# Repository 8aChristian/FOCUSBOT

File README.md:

# FOCUSBOT: Open-Source Autonomous AI Desktop Companion Robot

<p align="center">

</p>

---

## 📖 Índice General

1. [Descripción del Proyecto](#-descripción-del-proyecto)
2. [Arquitectura Mecánica y Carcasa DFA](#-arquitectura-mecánica-y-carcasa-dfa)
3. [Guía de Impresión 3D](#-guía-de-impresión-3d-paso-a-paso)
4. [Guía de Ensamblaje Mecatrónico](#-guía-de-ensamblaje-mecatrónico-paso-a-paso)
5. [Arquitectura Electrónica y PCBs](#-arquitectura-electrónica-y-pcbs)
6. [Guía de Carga de Firmware (PlatformIO)](#-guía-de-carga-de-firmware)
7. [Configuración de la IA y APIs de LLM](#-configuración-de-la-ia-y-apis-de-llm)
8. [Expresiones de Ojos y Movimientos Cutes](#-expresiones-de-ojos-y-movimientos-cutes)
9. [Lista de Materiales (BOM)](#-lista-de-materiales-bom)
10. [Licencia y Comunidad](#-licencia-y-comunidad)

---

## 🤖 Descripción del Proyecto

**FocusBot** es un robot de escritorio autónomo, compacto (**8.0 cm** de altura) y de código abierto diseñado como compañero de productividad, estudio e investigación mecatrónica. Equipado con visión por computadora, cuello articulado, locomoción diferencial, sintetizador de audio digital, micrófono MEMS y una pantalla IPS panorámica de 2.0 pulgadas con ojos procedurales bio-inspirados estilo Cozmo/Anki, FocusBot monitoriza tus sesiones de estudio, previene la procrastinación y te acompaña con una personalidad tierna y robótica mediante Modelos de Lenguaje (LLMs).

Es **100% Hardware y Software Libre**, optimizado para fabricarse con impresoras 3D domésticas (FDM/Resina) y PCBs de 2 capas estándar.

---

## 📐 Arquitectura Mecánica y Carcasa DFA

FocusBot incorpora una arquitectura monocoque **Top-Down DFA (Design for Assembly)** modelada en FreeCAD con el núcleo Open CASCADE:

### Características Clave de la Carcasa:
- **Carcasa Frontal Monolítica**: La cabeza frontal (`Carcasa_Cabeza_Frontal`) unifica el marco del visor y la estructura en una sola pieza sin juntas perimetrales ni holguras defectuosas. Cuenta con ventana activa de $43.5 \times 23.0\text{ mm}$ ($R=2.0\text{ mm}$) que aloja el panel LCD ST7789V de 2.0", y un orificio coaxial $\varnothing 2.6\text{ mm}$ para la cámara OV2640 a $Z = 71.0\text{ mm}$.
- **Orejas de Gato Bajas y Orgánicas**: Orejas curvadas y redondeadas de $5.3\text{ mm}$ de elevación sobre el techo, con cierre en vértice suave (cero tapas cónicas ni discos planos).
- **Difusor LED de Pecho en Forma Stadium (Cápsula Redondeada)**: Ranura frontal horizontal en el pecho de $19.6 \times 5.4\text{ mm}$ con bisel embutido de $23.6 \times 7.8\text{ mm}$ y pinhole de micrófono centrado arriba ($Z = 32.2\text{ mm}$), diseñada para emitir el brillo cyan característico del robot.
- **Tornillería Invisible y Cierre Bottom-Up**: La tapa del torso se fija mediante 4 tornillos M2 introducidos desde la base inferior hacia bosses ciegos en la cúpula, dejando el capó exterior 100% limpio y liso.
- **Cuello Flotante sin Fricción**: Holgura perimetral de aire de $0.80\text{ mm}$ entre cabeza y torso alrededor de una tornamesa de $\varnothing 18.0\text{ mm}$, garantizando rotación libre de -90° a +90° con $0.0000\text{ mm}^3$ de colisión.
- **Plano de Suelo Cinemático ($Z = 0.00\text{ mm}$)**: 4 puntos de apoyo coplanares formados por 2 ruedas cilíndricas lisas de tracción ($\varnothing 34.0\text{ mm}$) y 2 bolas de rodamiento omnidireccionales de acero ($\varnothing 8.0\text{ mm}$).

---

## 🖨️ Guía de Impresión 3D Paso a Paso

Todas las piezas se encuentran en formato `.stl` y `.step` en [`cad/stl/`](cad/stl/) y [`cad/3d_print_ready/`](cad/3d_print_ready/).

### Tabla de Piezas y Materiales:

| Pieza STL | Archivo STL | Material Recomendado | Color | Cant. | Soportes |
| :--- | :--- | :--- | :--- | :---: | :---: |
| **Cabeza Frontal** | `01_Carcasa_Cabeza_Frontal.stl` | PLA+ / PETG | Blanco Mate / Crema | 1 | No |
| **Cabeza Trasera + Orejas** | `02_Carcasa_Cabeza_Trasera.stl` | PLA+ / PETG | Blanco Mate / Crema | 1 | Solo en cuello (árbol) |
| **Chasis Torso Base** | `03_Carcasa_Torso_Chasis.stl` | PLA+ / PETG | Blanco Mate / Crema | 1 | No (apoyo plano) |
| **Tapa Superior Torso** | `04_Carcasa_Torso_Tapa.stl` | PLA+ / PETG | Blanco Mate / Crema | 1 | No |
| **Difusor LED Pecho** | `06_Difusor_Luz_Pecho.stl` | PETG Translúcido / Resina Clear | Blanco Natural / Clear | 1 | No |
| **Rueda Tracción Izq.** | `07_Rueda_Traccion_L.stl` | PLA+ o TPU 95A | Negro / Gris Oscuro | 1 | No |
| **Rueda Tracción Der.** | `08_Rueda_Traccion_R.stl` | PLA+ o TPU 95A | Negro / Gris Oscuro | 1 | No |
| **Aro Rueda Izq.** | `09_Aro_Cyan_Rueda_L.stl` | PLA | Cyan / Azul Eléctrico | 1 | No |
| **Aro Rueda Der.** | `10_Aro_Cyan_Rueda_R.stl` | PLA | Cyan / Azul Eléctrico | 1 | No |

### Parámetros Óptimos de Laminación (PrusaSlicer / Bambu Studio / Cura / OrcaSlicer):
- **Altura de capa (Layer Height)**: `0.16 mm` (o `0.12 mm` para la cabeza frontal para lograr máxima suavidad en el marco de la pantalla).
- **Perímetros / Paredes**: `4 perímetros` (mínimo `1.6 mm` de grosor de pared para asegurar la firmeza de las roscas de tornillos M2).
- **Relleno (Infill)**: `20% a 25% Gyroid` o Honeycomb.
- **Capas superiores e inferiores**: 5 capas sólidas arriba, 4 abajo.
- **Soportes**: Desactivados por defecto. Si tu impresora tiene puentes limitados, activa únicamente **Tree Supports (Soportes Tipo Árbol)** con ángulo de voladizo de >60° en la carcasa trasera de la cabeza.
- **Orientación de impresión**:
  - `Carcasa_Torso_Chasis`: Base plana hacia la cama de impresión.
  - `Carcasa_Torso_Tapa`: Superficie plana de partición hacia la cama.
  - `Carcasa_Cabeza_Frontal`: Cara frontal orientada hacia arriba o cara plana de unión hacia la cama.
  - `Ruedas`: Cara externa plana asentada en la cama.

---

## 🛠️ Guía de Ensamblaje Mecatrónico Paso a Paso

```mermaid
flowchart TD
    A["1. Chasis Inferior: Insertar 2x Bolas 8mm y 2x Motores N20"] --> B["2. Batería: Colocar LiPo 500mAh en su bahía inferior"]
    B --> C["3. Mainboard: Fijar PCB con 4x M2x4mm y conectar motores"]
    C --> D["4. Pecho: Insertar difusor LED stadium en la ranura frontal"]
    D --> E["5. Torso: Cerrar Tapa y atornillar con 4x M2x10mm desde abajo"]
    E --> F["6. Cabeza: Asentar LCD 2.0'', cámara OV2640 y Headboard PCB"]
    F --> G["7. Instalar servo SG90 y parlante 1511 en carcasa trasera"]
    G --> H["8. Conectar FPC 24 pines a través del cuello rotativo"]
    H --> I["9. Cerrar cabeza con 4x M2x8mm y acoplar al servo horn"]
```

### Paso 1: Chasis Inferior y Locomoción
1. Inserta a presión las dos **bolas de rodamiento omnidireccionales de acero de $\varnothing 8.0\text{ mm}$** en sus alojamientos semiesféricos frontal y trasero del chasis base.
2. Coloca los dos **motores N20** en sus cunas laterales orientando los ejes hacia los orificios de rueda.
3. Introduce la **batería LiPo 1S de 500 mAh** ($38 \times 20 \times 7\text{ mm}$) en la bahía del suelo.

### Paso 2: Instalación de la Mainboard PCB
1. Posiciona la placa principal (`hardware/mainboard/focusbot_mainboard.kicad_pcb`) sobre los 4 pilares MH1-MH4 a $Z = 23.5\text{ mm}$.
2. Asegúrate de que el conector USB-C y el interruptor SW1 encajen perfectamente en sus aberturas traseras.
3. Atornilla la PCB con 4 tornillos M2 de 4 mm.
4. Suelda o conecta los terminales de los motores N20 a los pads `MOT_L` y `MOT_R` y el conector JST de la batería LiPo.

### Paso 3: Cierre del Torso y Difusor Frontal
1. Inserta a presión el **Difusor de luz de pecho** (`06_Difusor_Luz_Pecho.stl`) en la ranura redondeada frontal.
2. Pasa el cable plano FFC/FPC de 24 pines desde la Mainboard hacia arriba a través del conducto central de la tornamesa.
3. Coloca la **Carcasa Torso Tapa** sobre el chasis e introduce **4 tornillos M2 de 10 mm desde la parte inferior** del chasis para unir ambas mitades sólidamente.
4. Fija el brazo del servo (horn de 1 brazo) en el cajeado de la tornamesa con 2 tornillos M1.7.

### Paso 4: Ensamblaje de la Cabeza
1. En la **Carcasa Cabeza Frontal**, asienta el panel LCD ST7789V de 2.0" en su cuna interior cuidando que quede centrado con la ventana de visualización.
2. Coloca la cámara OV2640 en el cajeado superior con su lente alineado al orificio pinhole de $Z = 71.0\text{ mm}$.
3. Desliza la **Headboard PCB** verticalmente por las guías laterales hasta topar con el panel.
4. En la **Carcasa Cabeza Trasera**, monta el **micro-servo SG90** invertido (eje hacia abajo) fijándolo con 2 tornillos a sus aletas, y coloca el parlante miniatura 1511 en su alojamiento.
5. Conecta el cable FPC de 24 pines al conector ZIF de la Headboard.
6. Cierra la cabeza introduciendo **4 tornillos M2 de 8 mm** desde los avellanados de la carcasa trasera.
7. Presiona la cabeza sobre el eje estriado del servo acoplado a la tornamesa del torso.
8. Coloca a presión las ruedas de tracción y sus aros decorativos cyan en los ejes D-shaft de los motores N20.

---

## ⚡ Arquitectura Electrónica y PCBs

FocusBot cuenta con dos placas de circuito impreso diseñadas en KiCad 10 con **0 violaciones de DRC y 0 conexiones huérfanas**:

<p align="center">
  &nbsp;
  
</p>

### Distribución de Pines del ESP32-S3:

| Periférico | Función | Pines ESP32-S3 | Bus / Protocolo |
| :--- | :--- | :--- | :--- |
| **Pantalla LCD 2.0"** | ST7789V IPS (320x240) | MOSI: `GPIO35`, SCLK: `GPIO36`, DC: `GPIO47`, CS: `GPIO48` | SPI a 40 MHz |
| **Cámara IA** | OV2640 2MP DVP | SIOC: `GPIO4`, SIOD: `GPIO5`, XCLK: `GPIO6`, PCLK: `GPIO7`, HREF: `GPIO14`, VSYNC: `GPIO43`, D0-D7: `GPIO37,38,39,40,41,42,2,1` | DVP 8-bit + SCCB |
| **Audio DAC** | MAX98357A (Parlante) | BCLK: `GPIO12`, WS: `GPIO11`, DIN: `GPIO10` | I2S Digital |
| **Micrófono MEMS** | INMP441 (Voz / Caricias) | BCLK: `GPIO12`, WS: `GPIO11`, DOUT: `GPIO13` | I2S Digital |
| **Motores DC** | DRV8833 Dual H-Bridge | L_IN1: `GPIO15`, L_IN2: `GPIO16`, R_IN1: `GPIO17`, R_IN2: `GPIO18` | PWM 20 kHz (LEDC) |
| **Servo Cuello** | SG90 Pan (Giro Horiz.) | PWM: `GPIO21` | Servo 50 Hz |
| **Sensor Batería** | Divisor 1:2 LiPo | ADC: `GPIO44` | ADC1 Canal 3 |
| **Puerto Nativo USB** | Flasheo / JTAG / CDC | D-: `GPIO19`, D+: `GPIO20` | USB 2.0 FS Nativo |

---

## 💻 Guía de Carga de Firmware

El ESP32-S3-WROOM-1 cuenta con **controlador USB nativo en silicio**. No necesitas adaptadores UART externos (CH340/CP2102); la placa se programa directamente con un cable USB-C estándar conectado a la PC.

### Requisitos Previos:
1. Instalar [Visual Studio Code](https://code.visualstudio.com/).
2. Instalar la extensión **PlatformIO IDE** en VS Code (o instalar PlatformIO CLI vía `pip install platformio`).
3. Clonar este repositorio y abrir la carpeta del proyecto en VS Code.

### Compilación y Subida:

1. Abre una terminal en la raíz del proyecto y entra en `firmware`:
   ```powershell
   cd firmware
   ```

2. **Compilar el código**:
   ```powershell
   pio run
   ```
   *El sistema descargará automáticamente el toolchain de Espressif, FreeRTOS y las librerías necesarias.*

3. **Cargar el firmware en el robot**:
   Conecta FocusBot a la PC mediante el cable USB-C, enciende el interruptor SW1 y ejecuta:
   ```powershell
   pio run -t upload
   ```

4. **Abrir monitor serie para ver diagnósticos**:
   ```powershell
   pio device monitor -b 115200
   ```

> [!TIP]
> **Modo Bootloader Manual (en caso de puerto bloqueado):**
> Si el puerto COM no responde al flashear: mantén presionado el botón `BOOT` (SW_BOOT en la PCB), presiona y suelta el botón `RESET`, luego suelta `BOOT`. El ESP32-S3 entrará en modo de descarga forzado por hardware.

---

## 🧠 Configuración de la IA y APIs de LLM

FocusBot puede interactuar con Inteligencia Artificial conversacional a través de dos métodos:

### Método 1: App Móvil Companion por Bluetooth (Recomendado)
El robot actúa como periférico Bluetooth Low Energy (`FocusBot-Companion`). La aplicación en el teléfono procesa el audio con reconocimiento de voz y llama a la API de tu modelo preferido (ChatGPT, Claude o Gemini). La app retransmite el texto al robot, el cual parsea automáticamente las etiquetas de actuación.

### Método 2: Wi-Fi Directo en el Microcontrolador
Si deseas que el propio robot se conecte a internet y llame a las APIs directamente:

1. Ve a la carpeta `firmware/include/`.
2. Copia el archivo de ejemplo:
   ```powershell
   Copy-Item firmware/include/credentials.h.example firmware/include/credentials.h
   ```
3. Abre `firmware/include/credentials.h` y coloca tus credenciales:
   ```cpp
   // Red Wi-Fi
   #define FOCUSBOT_WIFI_SSID       "Mi_Casa_WiFi"
   #define FOCUSBOT_WIFI_PASSWORD   "MiContrasenaSegura"

   // Proveedor seleccionado ("OPENAI" | "GEMINI" | "CLAUDE" | "OLLAMA_LOCAL")
   #define LLM_PROVIDER             "OPENAI"

   // API Keys según tu cuenta:
   #define OPENAI_API_KEY           "sk-proj-xxxxxxxxxxxxxxxxxxxxxxxxxxxxxxxx"
   #define GEMINI_API_KEY           "AIzaSyxxxxxxxxxxxxxxxxxxxxxxxxxxxxxx"
   #define CLAUDE_API_KEY           "sk-ant-api03-xxxxxxxxxxxxxxxxxxxxxxxxx"
   ```

### Personalidad del Robot (System Prompt):
El archivo [`firmware/include/focusbot_llm_persona.h`](firmware/include/focusbot_llm_persona.h) contiene el prompt del sistema que define su comportamiento:
- **Voz y tono**: Robot cute, tierno, infantil pero inteligente, con sonidos robóticos cortos (*"bip bop!"*, *"whirrr"*).
- **Control de Actuación por Etiquetas**: El LLM emite etiquetas entre corchetes que el firmware traduce en hardware físico instantáneamente:

```text
[HAPPY]   -> Ojos cyan felices y alegres
[GLEE]    -> Arcos gigantes de felicidad extrema + sacudida de cuerpo
[AWE]     -> Ojos enormes brillantes de asombro + inclinación de cabeza
[WINK]    -> Guiño cómplice de un solo ojo
[HEART]   -> Ojos de corazones magenta + ronroneo
[WORRIED] -> Ojos preocupados (alerta cuando el usuario abandona la mesa)
[ANGRY]   -> Ojos rojos y ceño fruncido (alerta de procrastinación/celular)
[NOD]     -> Movimiento vertical del cuello diciendo "Sí"
[SHAKE]   -> Movimiento horizontal del cuello diciendo "No"
[TILT]    -> Inclinación lateral curiosa de la cabeza
[WIGGLE]  -> Bailecito de izquierda a derecha con las ruedas
[SPIN]    -> Giro de 360 grados de festejo
```

---

## 👀 Expresiones de Ojos y Movimientos Cutes

El motor visual procedural ([`display_engine.cpp`](firmware/src/display_engine.cpp)) implementa **31 estados emocionales** con renderizado multi-capa a 50 Hz en la pantalla IPS:

- **Efecto Glow Multi-capa**: Halo exterior atenuado, anillo medio difuso, núcleo cyan brillante, reflejos especulares orgánicos dobles y pupila oscura interior.
- **Seguimiento Facial en Tiempo Real**: La cámara OV2640 calcula el centroide de movimiento del usuario y los ojos lo siguen suavemente en los ejes X e Y (`setLookTarget(nx, ny)`).
- **Detector de Caricias (Petting Sensor)**: Al tocar suavemente la cabeza del robot, el micrófono MEMS detecta el patrón acústico de toque y activa ronroneo sintetizado con ojos de corazón.
- **Milestones de Concentración**: Cada 25 minutos de estudio continuo sin distracciones, el robot reproduce una fanfarria triunfal, sus ojos se tornan verde esmeralda brillante (`ILLUM_GREEN_WIN`) y ejecuta un giro de victoria (`spinJoy()`).

---

## 📋 SuperBOM: Lista Maestra de Componentes, Enlaces y Costos

Guía de compra optimizada para **máximo ahorro**, priorizando la fabricación de placas vírgenes (*bare PCBs*) y la adquisición de componentes por separado sin ensamblaje costoso de fábrica.

---

### 1. Componentes Externos (Modulares / Sin soldar a placa)

Se conectan directamente a las placas mediante cables y conectores:

| Componente | Enlaces de Compra Directa | Rango de Precio Estimado | Formato Habitual |
| :--- | :--- | :---: | :--- |
| **Batería LiPo 3.7V 500mAh**<br>(Conector JST-PH 2.0 mm) | • [AliExpress (Opción Económica)](https://www.aliexpress.com/item/32814862683.html)<br>• [Amazon (Envío Rápido)](https://www.amazon.com/dp/B0D3F67N6F) | **$4.00 – $9.00 USD** | Unidad con circuito de protección PCM integrado |
| **Micromotores N20 metálicos**<br>(6V 300 RPM con reductora) | • [AliExpress (N20 Gearmotor)](https://www.aliexpress.com/item/1005005519903657.html) | **$1.50 – $2.50 USD** | Por unidad (se requieren 2: Izquierdo y Derecho) |
| **Cables chicote JST-SH 1.0 mm**<br>(2 pines pre-crimpeados para motores/parlante) | • [AliExpress (Cables JST-SH 1.0 mm)](https://www.aliexpress.com/item/1005011595323701.html) | **$1.50 – $2.50 USD** | Paquete de 10 a 20 cables con conector hembra |
| **Micro-servo SG90 9g**<br>(Giro horizontal de cuello) | • [Amazon (Opción 1)](https://www.amazon.com/dp/B07L2SF3R4)<br>• [Amazon (Opción Alternativa)](https://www.amazon.com/dp/B01M5LIKLQ) | **$2.50 – $4.00 USD** | Unidad individual con juego de brazos/horns |
| **Micro-Parlante 1511**<br>(8 $\Omega$ 1W, $15 \times 11 \times 3.5\text{ mm}$) | • [AliExpress (Parlante 1511 Box)](https://www.aliexpress.com/i/1680403579.html) | **$0.90 – $1.70 USD** | Unidad suelta o lote de 5 a 10 piezas ($2.50 - $3.50) |
| **Cámara OV2640**<br>(Flex cinta 24 pines paso 0.5 mm) | • [AliExpress (OV2640 Módulo Cámara)](https://www.aliexpress.com/wholesale?catId=0&SearchText=OV2640) | **$2.80 – $4.50 USD** | Módulo de cámara con lente estándar |
| **Pantalla IPS LCD ST7789 2.0"**<br>(SPI 240x320, bare panel) | • [AliExpress (ST7789 2.0" IPS)](https://www.aliexpress.com/item/1005009314410563.html)<br>• [AliExpress (Opción Alternativa)](https://www.aliexpress.com/item/1005012615180387.html) | **$3.50 – $5.50 USD** | Panel individual IPS 240x320 |

---

### 2. Elementos de Interconexión Flexible y Zócalos ZIF

| Componente | Enlaces de Compra Directa | Rango de Precio Estimado | Formato Habitual |
| :--- | :--- | :---: | :--- |
| **Cable plano flexible FPC 24 pines**<br>(Paso 0.5 mm, Tipo A o Tipo B) | • [AliExpress (FPC 24P 0.5 mm)](https://www.aliexpress.com/i/1005006038283095.html)<br>• [AliExpress (Opción Alternativa)](https://www.aliexpress.com/i/4000022157163.html) | **$0.50 – $1.00 USD** | Paquete de 2 a 5 cables |
| **Conector ZIF 24 pines 0.5 mm SMD**<br>(Seguro abatible / Bottom Contact) | • [AliExpress (ZIF 24P 0.5 mm)](https://www.aliexpress.com/i/1005004233136813.html)<br>• [AliExpress (Opción Alternativa)](https://www.aliexpress.com/item/32850399481.html) | **$1.50 – $2.50 USD** | Tira o lote de 10 conectores para placa |
| **Conector hembra USB-C SMD 16 pines**<br>(Carga y datos nativos) | • [AliExpress (USB-C 16P SMD)](https://www.aliexpress.com/i/1005006257173539.html) | **$1.70 – $2.50 USD** | Lote de 5 a 10 conectores hembra |

---

### 3. Circuitos Integrados y Semiconductores para Soldar (SMD)

Comprados sueltos o en lote económico para soldar manualmente o con pasta de estaño y aire caliente:

| Componente / Circuito Integrado | Enlace Catálogo JLCPCB / LCSC / AliExpress | Precio Unitario Estimado |
| :--- | :--- | :---: |
| **ESP32-S3-WROOM-1-N8R8 / N16R8** | • [JLCPCB (C2913201)](https://jlcpcb.com/partdetail/3198299-ESP32_S3_WROOM_1N8R8/C2913201)<br>• [LCSC (C2913201)](https://www.lcsc.com/product-detail/C2913201.html) | **$3.50 – $4.40 USD** |
| **DRV8833PWP (Driver Puente H Dual)** | • [AliExpress (Chips DRV8833)](https://www.aliexpress.com/item/1005008600208107.html)<br>• [AliExpress (Opción 2)](https://www.aliexpress.com/item/1005005236496976.html) | **$0.70 – $1.30 USD** |
| **TP4056 (Cargador LiPo)** | • [AliExpress / LCSC](https://www.aliexpress.com/item/1005008600208107.html) | **$0.15 – $0.30 USD** |
| **DW01A + FS8205A (Protección LiPo)** | • LCSC / AliExpress (SOT-23-6 / TSSOP-8) | **$0.10 – $0.25 USD** |
| **SY8089AAAC (Regulador Step-Down 2A)** | • [LCSC (C78988)](https://www.lcsc.com/product-detail/DC-DC-Converters_Silergy-Corp-SY8089AAAC_C78988.html) | **$0.20 – $0.40 USD** |
| **MAX98357AETE+T (Amplificador I2S)** | • [JLCPCB (C910544)](https://jlcpcb.com/partdetail/MaximIntegrated-MAX98357AETET/C910544)<br>• [LCSC (C910544)](https://www.lcsc.com/product-detail/C910544.html) | **$0.90 – $1.20 USD** |
| **MPU-6050 (IMU 6 Ejes)** | • JLCPCB / LCSC / AliExpress (QFN-24) | **$1.20 – $2.20 USD** |
| **INMP441 (Micrófono MEMS LGA-9)** | • [AliExpress (INMP441 SMD suelto)](https://he.aliexpress.com/item/1005007633632817.html) | **$1.50 – $3.00 USD** |
| **Componentes Pasivos y Discretos 0603**<br>(Inductor 2.2µH, AO3401A, SS14, BAT54, R, C) | • Kits surtidos 0603 en AliExpress / LCSC | **$0.50 – $1.50 USD**<br>*(costo total agrupado)* |

---

### 4. Fabricación de PCBs y Costo de Impresión 3D

| Ítem | Proveedor / Proceso | Detalle de Costo | Costo por Robot |
| :--- | :--- | :--- | :---: |
| **Mainboard PCB (Placa Virgen)** | JLCPCB / PCBWay (2 capas, FR4) | Pedido estándar de 5 placas por **$2.00 USD** | **$0.40 – $1.00 USD** |
| **Headboard PCB (Placa Virgen)** | JLCPCB / PCBWay (2 capas, FR4) | Pedido estándar de 5 placas por **$2.00 USD** | **$0.40 – $1.00 USD** |
| **Carcasa Impresa en 3D** | Impresora FDM doméstica (PLA+ / PETG / TPU) | Consumo total de filamento: ~110–130 gramos (carcasa, ruedas, difusor) a ~$18–$22/kg | **$2.00 – $3.00 USD** |
| **Tornillería y Bolas de Rodamiento** | 8x Tornillos M2 + 2x Bolas acero 8 mm | Comprados en ferretería o kit surtido M2 | **$0.80 – $1.50 USD** |

---

### 💰 Resumen de Inversión Global (Total Build Cost)

*Sin incluir gastos de envío internacional:*

| Categoría | Rango de Costo (USD) |
| :--- | :---: |
| **1. Componentes Modulares Externos** (Cámara, LCD, servo, 2 motores N20, batería LiPo, parlante y cables) | **$20.00 – $32.00 USD** |
| **2. Circuitos Integrados y Semiconductores SMD** | **$9.00 – $15.00 USD** |
| **3. Placas de Circuito Impreso Vírgenes (Mainboard + Headboard)** | **$0.80 – $2.00 USD** |
| **4. Materiales de Impresión 3D y Tornillería** | **$2.80 – $4.50 USD** |
| **COSTO TOTAL ESTIMADO POR ROBOT COMPLETO** | **$32.60 – $53.50 USD** |

---

## 🌐 Licencia y Comunidad

FocusBot es un proyecto de hardware y software libre bajo las siguientes licencias:
- **Hardware**: [CERN-OHL-S v2 (Strongly Reciprocal)](https://ohwr.org/cern_ohl_s_v2.txt)
- **Firmware y Software**: [Licencia MIT](LICENSE)
- **Documentación y Gráficos**: [CC BY-SA 4.0](https://creativecommons.org/licenses/by-sa/4.0/)

¿Quieres colaborar? Puedes aportar mejoras al enrutamiento de PCB, soporte para Micro-ROS, modelos de visión neuronal ligera o accesorios personalizados para el chasis mediante Issues y Pull Requests.

---

<p align="center">
  <b>Diseñado con ingeniería de precisión para la comunidad maker y de robótica libre.</b><br>
  <sub>Mantenido por 8aChristian y colaboradores.</sub>
</p>

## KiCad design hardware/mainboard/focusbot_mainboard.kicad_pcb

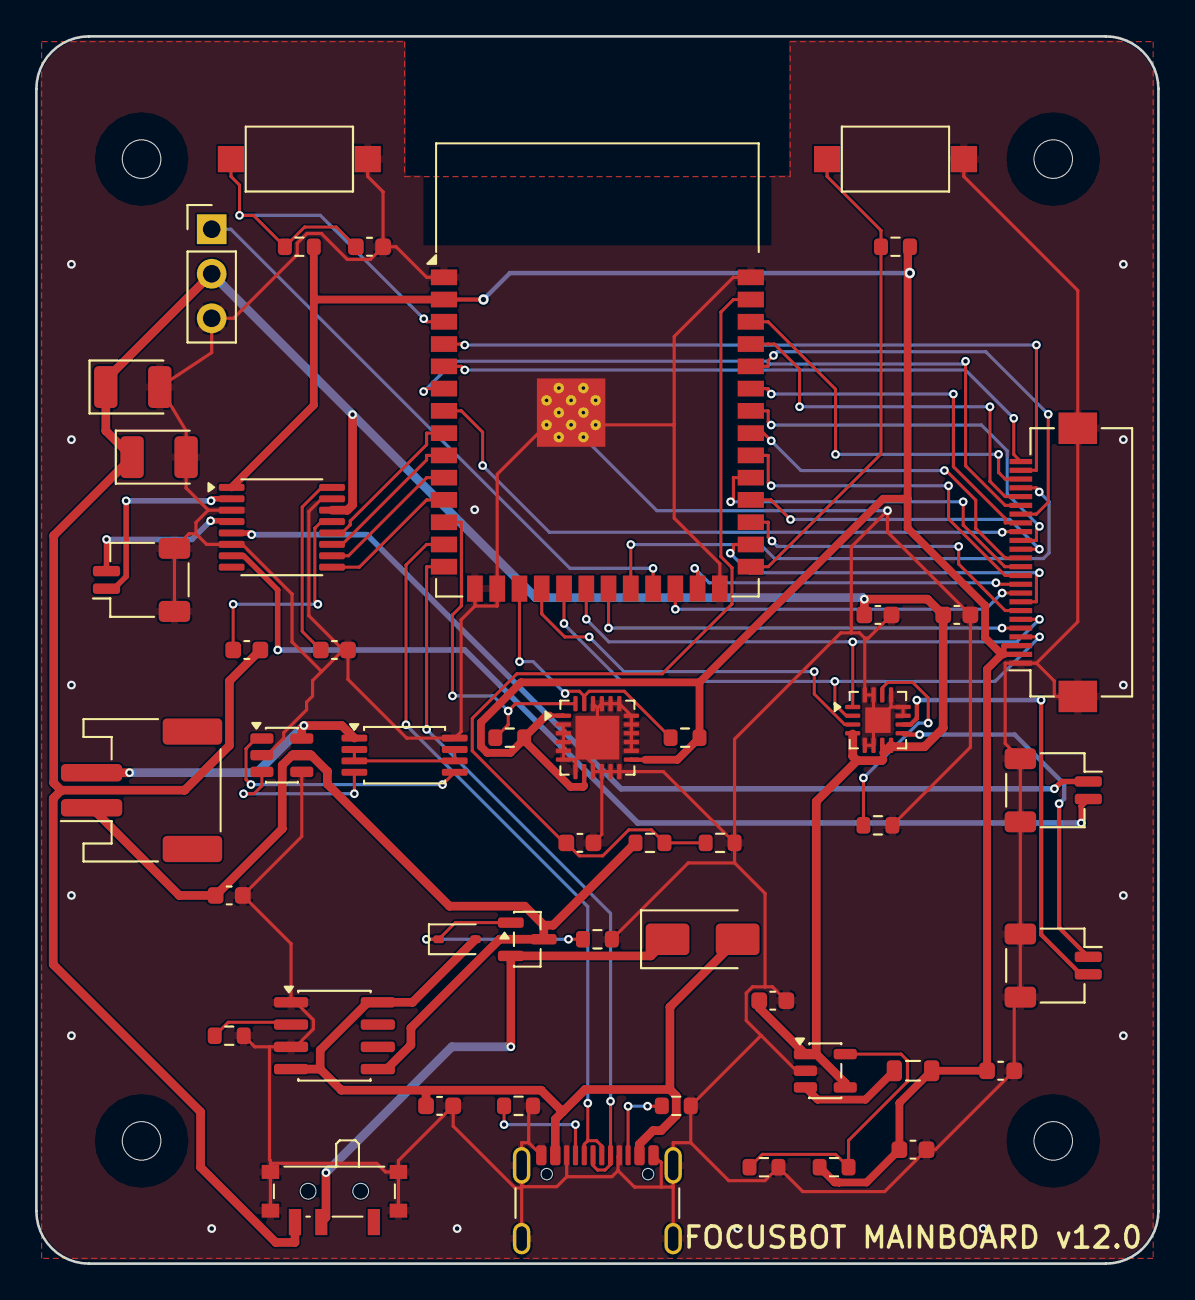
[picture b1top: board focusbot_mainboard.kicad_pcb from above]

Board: 2 copper layers, 64.0 x 70.0 mm, 52 parts (0 on the bottom side), 59 nets.

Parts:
C_ADC: 100nF; C_0603_1608Metric
C_BAT: 10uF; C_0603_1608Metric
C_EN: 100nF; C_0603_1608Metric
C_IN_BUCK: 10uF; C_0603_1608Metric
C_OUT_BUCK1, C_OUT_BUCK2: 22uF; C_0603_1608Metric
C_SERVO: 100uF; CP_EIA-3528-21_Kemet-B
C_SPK1: 10uF; C_0603_1608Metric
C_SPK2: 100nF; C_0603_1608Metric
C_VBUS: 10uF; C_0603_1608Metric
C_VCP: 10nF; C_0603_1608Metric
C_VINT: 2.2uF; C_0603_1608Metric
C_VM: 47uF_10V; CP_EIA-3528-21_Kemet-B
D1: SS14; D_SMA
D2: BAT54; D_SOD-323
J_BATT: LiPo_Batt; JST_PH_S2B-PH-SM4-TB_1x02-1MP_P2.00mm_Horizontal
J_FPC: FPC_24P; Hirose_FH12-24S-0.5SH_1x24-1MP_P0.50mm_Horizontal
J_M1: Motor_Left; JST_SH_SM02B-SRSS-TB_1x02-1MP_P1.00mm_Horizontal
J_M2: Motor_Right; JST_SH_SM02B-SRSS-TB_1x02-1MP_P1.00mm_Horizontal
J_SERVO: Servo_Neck; PinHeader_1x03_P2.54mm_Vertical
J_SPK: Speaker_1511; JST_SH_SM02B-SRSS-TB_1x02-1MP_P1.00mm_Horizontal
J_USB: USB-C-16P; USB_C_Receptacle_GCT_USB4105-xx-A_16P_TopMnt_Horizontal
L1: 2.2uH; L_0805_2012Metric
MH1, MH2, MH3, MH4: M2; MountingHole_2.2mm_M2
Q1: AO3401A; SOT-23
R_BAT1, R_BAT2: 100k_1%; R_0603_1608Metric
R_BOOT: 10k; R_0603_1608Metric
R_CC1, R_CC2: 5.1k; R_0603_1608Metric
R_EN: 10k; R_0603_1608Metric
R_FB1: 100k; R_0603_1608Metric
R_FB2: 22k; R_0603_1608Metric
R_GAIN: 100k; R_0603_1608Metric
R_GATE: 100k; R_0603_1608Metric
R_PROG: 1.6k; R_0603_1608Metric
R_SCL: 4.7k; R_0603_1608Metric
R_SDA: 4.7k; R_0603_1608Metric
SW1: Power_Switch; SW_SPDT_PCM12
SW_BOOT: SW_BOOT; SW_SPST_CK_RS282G05A3
SW_RST: SW_RST; SW_SPST_CK_RS282G05A3
U1: ESP32-S3-WROOM-1-N16R8; ESP32-S3-WROOM-1
U2: TP4056; SOIC-8_3.9x4.9mm_P1.27mm
U3: DW01A; SOT-23-6
U4: FS8205A; TSSOP-8_4.4x3mm_P0.65mm
U5: SY8089AAAC; SOT-23-5
U6: DRV8833PWP; TSSOP-16_4.4x5mm_P0.65mm
U7: MAX98357A; QFN-16-1EP_3x3mm_P0.5mm_EP1.45x1.45mm
U8: MPU-6050; HVQFN-24-1EP_4x4mm_P0.5mm_EP2.5x2.5mm

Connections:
3V3: C_OUT_BUCK1.1, C_OUT_BUCK2.1, J_FPC.2, J_FPC.3, L1.2, R_BOOT.2, R_EN.2, R_FB1.1, R_SCL.2, R_SDA.2, U1.2, U6.1, U8.1, U8.8, U8.13
BATT_MINUS: J_BATT.2, U3.6, U4.1
BAT_ADC: C_ADC.1, R_BAT1.2, R_BAT2.1, U1.39
BUCK_FB: R_FB1.2, R_FB2.1, U5.5
BUCK_LX: L1.1, U5.3
CAM_D0: J_FPC.14, U1.30
CAM_D1: J_FPC.12, U1.31
CAM_D2: J_FPC.11, U1.32
CAM_D3: J_FPC.13, U1.33
CAM_D4: J_FPC.15, U1.34
CAM_D5: J_FPC.17, U1.35
CAM_D6: J_FPC.18, U1.36
CAM_D7: J_FPC.20, U1.37
CAM_HREF: J_FPC.21, U1.22
CAM_PCLK: J_FPC.16, U1.7
CAM_SIOC: J_FPC.23, U1.4
CAM_SIOD: J_FPC.24, U1.5
CAM_VSYNC: J_FPC.22, U1.38
CAM_XCLK: J_FPC.19, U1.6
CHG_PROG: R_PROG.1, U2.2
DRV_VCP: C_VCP.1, U6.13
DRV_VINT: C_VINT.1, U6.16
FET_DRAIN: U4.2, U4.3, U4.6, U4.7
GND: C_ADC.2, C_BAT.2, C_EN.2, C_IN_BUCK.2, C_OUT_BUCK1.2, C_OUT_BUCK2.2, C_SERVO.2, C_SPK1.2, C_SPK2.2, C_VBUS.2, C_VINT.2, C_VM.2, J_FPC.1, J_FPC.MP, J_M1.MP, J_M2.MP, J_SERVO.3, J_SPK.MP, J_USB.A1, J_USB.A8, J_USB.A12, J_USB.B1, J_USB.B8, J_USB.B12, J_USB.SH, R_BAT2.2, R_CC1.2, R_CC2.2, R_FB2.2, R_GAIN.2, R_GATE.2, R_PROG.2, SW_BOOT.2, SW_RST.2, U1.1, U1.15, U1.16, U1.26, U1.40, U1.41, U2.1, U2.3, U3.2, U3.4, U4.8, U5.2, U6.3, U6.6, U6.15, U7.5, U7.6, U7.11, U7.12, U7.13, U7.15, U7.16, U7.17, U8.2, U8.3, U8.4, U8.5, U8.6, U8.7, U8.9, U8.10, U8.11, U8.12, U8.14, U8.15, U8.16, U8.17, U8.18, U8.19, U8.20, U8.21, U8.22, U8.25
I2C_SCL: R_SCL.1, U1.17, U8.23
I2C_SDA: R_SDA.1, U1.12, U8.24
I2S_BCLK: J_FPC.6, U1.20, U7.1
I2S_MIC_DATA: J_FPC.5, U1.21
I2S_SPK_DATA: U1.18, U7.3
I2S_WS: J_FPC.4, U1.19, U7.2
LCD_CS: J_FPC.10, U1.25
LCD_DC: J_FPC.9, U1.24
LCD_MOSI: J_FPC.8, U1.28
LCD_SCLK: J_FPC.7, U1.29
LOAD_GATE: D2.1, Q1.1, R_GATE.1
MCU_BOOT: R_BOOT.1, SW_BOOT.1, U1.27
MCU_EN: C_EN.1, R_EN.1, SW_RST.1, U1.3
MOTOR_L_IN1: U1.8, U6.12
MOTOR_L_IN2: U1.9, U6.11
MOTOR_L_OUT1: J_M1.1, U6.2
MOTOR_L_OUT2: J_M1.2, U6.4
MOTOR_R_IN1: U1.10, U6.10
MOTOR_R_IN2: U1.11, U6.9
MOTOR_R_OUT1: J_M2.1, U6.5
MOTOR_R_OUT2: J_M2.2, U6.7
OC_GATE: U3.3, U4.4
OD_GATE: U3.1, U4.5
SERVO_PWM: J_SERVO.1, U1.23
SPK_GAIN: R_GAIN.1, U7.14
SPK_OUTN: J_SPK.2, U7.10
SPK_OUTP: J_SPK.1, U7.9
USB_CC1: J_USB.A5, R_CC1.1
USB_CC2: J_USB.B5, R_CC2.1
USB_D+: J_USB.A6, J_USB.B6, U1.14
USB_D-: J_USB.A7, J_USB.B7, U1.13
VBAT: C_BAT.1, J_BATT.1, Q1.3, R_BAT1.1, U2.5, U3.5
VBUS: C_VBUS.1, D1.2, D2.2, J_USB.A4, J_USB.A9, J_USB.B4, J_USB.B9, U2.4, U2.8
VSYS: D1.1, Q1.2, SW1.2
VSYS_SW: C_IN_BUCK.1, C_SERVO.1, C_SPK1.1, C_SPK2.1, C_VCP.2, C_VM.1, J_SERVO.2, SW1.3, U5.1, U5.4, U6.14, U7.4, U7.7, U7.8

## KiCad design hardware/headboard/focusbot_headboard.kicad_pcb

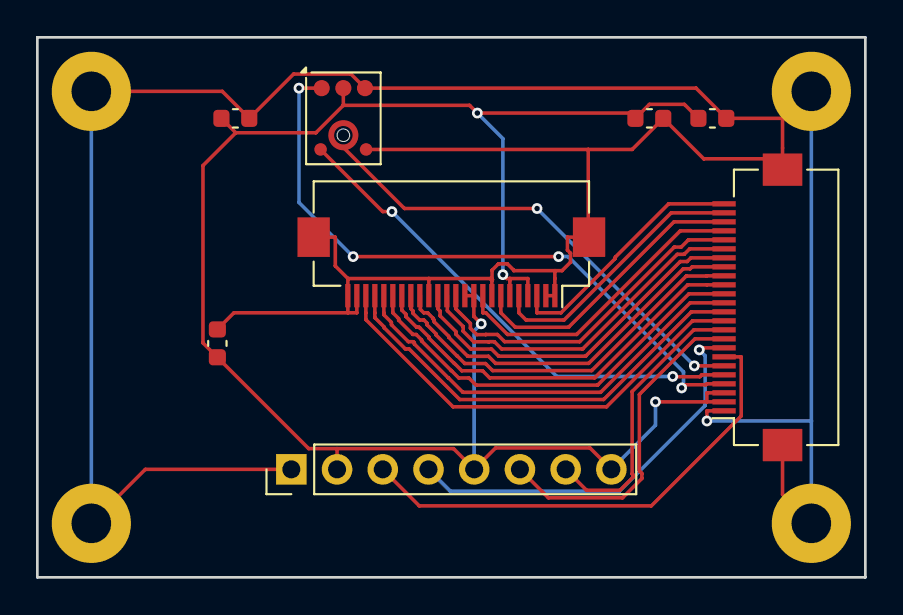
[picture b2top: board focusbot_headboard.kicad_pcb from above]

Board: 2 copper layers, 46.0 x 30.0 mm, 12 parts (0 on the bottom side), 23 nets.

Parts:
C_CAM1: 10uF; C_0603_1608Metric
C_CAM2: 100nF; C_0603_1608Metric
C_DISP: 10uF; C_0603_1608Metric
C_MIC: 100nF; C_0603_1608Metric
DISP1: ST7789; PinHeader_1x08_P2.54mm_Vertical
J_CAM: CAM_24P; Hirose_FH12-24S-0.5SH_1x24-1MP_P0.50mm_Horizontal
J_FPC_HEAD: FPC_24P; Hirose_FH12-24S-0.5SH_1x24-1MP_P0.50mm_Horizontal
MH1, MH2, MH3, MH4: M2; MountingHole_2.2mm_M2_Pad
MIC1: INMP441; Knowles_LGA-6_4.72x3.76mm

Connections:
3V3: C_CAM1.1, C_CAM2.1, C_DISP.1, C_MIC.1, DISP1.2, DISP1.5, DISP1.8, J_CAM.4, J_CAM.6, J_CAM.10, J_CAM.11, J_FPC_HEAD.2, J_FPC_HEAD.3, MIC1.6
CAM_D0: J_CAM.19, J_FPC_HEAD.14
CAM_D1: J_CAM.21, J_FPC_HEAD.12
CAM_D2: J_CAM.22, J_FPC_HEAD.11
CAM_D3: J_CAM.20, J_FPC_HEAD.13
CAM_D4: J_CAM.18, J_FPC_HEAD.15
CAM_D5: J_CAM.16, J_FPC_HEAD.17
CAM_D6: J_CAM.14, J_FPC_HEAD.18
CAM_D7: J_CAM.12, J_FPC_HEAD.20
CAM_HREF: J_CAM.9, J_FPC_HEAD.21
CAM_PCLK: J_CAM.17, J_FPC_HEAD.16
CAM_SIOC: J_CAM.5, J_FPC_HEAD.23
CAM_SIOD: J_CAM.3, J_FPC_HEAD.24
CAM_VSYNC: J_CAM.7, J_FPC_HEAD.22
CAM_XCLK: J_CAM.13, J_FPC_HEAD.19
GND: C_CAM1.2, C_CAM2.2, C_DISP.2, C_MIC.2, DISP1.1, J_CAM.1, J_CAM.2, J_CAM.8, J_CAM.15, J_CAM.23, J_CAM.24, J_CAM.MP, J_FPC_HEAD.1, J_FPC_HEAD.MP, MH1.1, MH2.1, MH3.1, MH4.1, MIC1.4, MIC1.5
LCD_CS: DISP1.7, J_FPC_HEAD.10
LCD_DC: DISP1.6, J_FPC_HEAD.9
LCD_MOSI: DISP1.4, J_FPC_HEAD.8
LCD_SCLK: DISP1.3, J_FPC_HEAD.7
MIC_SCK: J_FPC_HEAD.6, MIC1.3
MIC_SD: J_FPC_HEAD.5, MIC1.2
MIC_WS: J_FPC_HEAD.4, MIC1.1

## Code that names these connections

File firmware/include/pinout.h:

#pragma once
#include <Arduino.h>

// =============================================================================
// FOCUSBOT HARDWARE PINOUT ARCHITECTURE v12.0
// MCU: ESP32-S3-WROOM-1-N16R8 (16MB Flash, 8MB PSRAM Octal)
// =============================================================================

// --- 1. DRV8833 DUAL H-BRIDGE MOTOR CONTROLLER ---
#define PIN_MOTOR_L_IN1     15  // Left Motor Forward PWM
#define PIN_MOTOR_L_IN2     16  // Left Motor Reverse PWM
#define PIN_MOTOR_R_IN1     17  // Right Motor Forward PWM
#define PIN_MOTOR_R_IN2     18  // Right Motor Reverse PWM

// --- 2. SG90 PAN HEAD SERVO CONTROLLER ---
#define PIN_SERVO_PWM       21  // Head Pan Axis (0 to 180 deg)

// --- 3. I2C BUS (MPU-6050 6-DOF IMU) ---
#define PIN_I2C_SDA         8   // IMU SDA (2.2k pull-up)
#define PIN_I2C_SCL         9   // IMU SCL (2.2k pull-up)
#define MPU6050_I2C_ADDR    0x68

// --- 4. I2S DIGITAL AUDIO (MAX98357A DAC & INMP441 MEMS MIC) ---
#define PIN_I2S_BCLK        12  // Bit Clock (Shared Amp & Mic)
#define PIN_I2S_WS          11  // Word Select / LRC (Shared Amp & Mic)
#define PIN_I2S_SPK_DATA    10  // MAX98357A Audio Serial Data (DIN)
#define PIN_I2S_MIC_DATA    13  // INMP441 Audio Serial Data (DOUT)

// --- 5. ST7789 2.0" IPS DISPLAY (240x320, SPI) ---
#define PIN_LCD_MOSI        35  // Master Out Slave In
#define PIN_LCD_SCLK        36  // SPI Clock
#define PIN_LCD_DC          47  // Data / Command Select
#define PIN_LCD_CS          48  // Chip Select (Active Low)

// --- 6. OV2640 DVP AI VISION CAMERA ---
#define PIN_CAM_SIOC        4   // SCCB I2C Clock
#define PIN_CAM_SIOD        5   // SCCB I2C Data
#define PIN_CAM_XCLK        6   // External Clock (20MHz)
#define PIN_CAM_PCLK        7   // Pixel Clock
#define PIN_CAM_HREF        14  // Horizontal Reference
#define PIN_CAM_VSYNC       43  // Vertical Sync
#define PIN_CAM_D0          37  // Data Bit 0
#define PIN_CAM_D1          38  // Data Bit 1
#define PIN_CAM_D2          39  // Data Bit 2
#define PIN_CAM_D3          40  // Data Bit 3
#define PIN_CAM_D4          41  // Data Bit 4
#define PIN_CAM_D5          42  // Data Bit 5
#define PIN_CAM_D6          2   // Data Bit 6
#define PIN_CAM_D7          1   // Data Bit 7

// --- 7. POWER & SYSTEM TELEMETRY ---
#define PIN_BAT_ADC         44  // LiPo Voltage Sense (1:2 Voltage Divider)
#define PIN_BOOT_SW         0   // Native Boot/Flash Button
#define PIN_USB_DM          19  // USB Native D-
#define PIN_USB_DP          20  // USB Native D+

// Battery Constants (1S LiPo: 3.0V cut-off to 4.2V fully charged)
#define BAT_R1_OHMS         100000.0f
#define BAT_R2_OHMS         100000.0f
#define BAT_DIVIDER_RATIO   ((BAT_R1_OHMS + BAT_R2_OHMS) / BAT_R2_OHMS) // 2.0x
#define BAT_MIN_VOLTS       3.20f
#define BAT_MAX_VOLTS       4.20f
#define BAT_LOW_THRESHOLD   3.40f
